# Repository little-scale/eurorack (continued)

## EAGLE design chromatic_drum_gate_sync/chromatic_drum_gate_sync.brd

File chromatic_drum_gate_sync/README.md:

This Teensy-based project has 12 gate outputs that are set using note messages over USB MIDI. 

For USB MIDI Channel 1: 

Each note in the scale (C, C#, D, D# etc) corresponds to a gate output labelled G1 - G12, and will set high from a note on message and low from a note off message. This is useful for controlling twelve drum modules using the gate input on each module. 

For USB MIDI Channel 2: 

The first six notes in the scale (C, C#, D, D# etc) corresponds to a gate output labelled G1 - G6, and will set high from a note on message and low from a note off message. A velocity above 99 will also set a gate output labelled G7 - G12 high, with a velocity below or equal to 99 will also set a gate output labelled G7 - G12 low. This is useful for controlling six drum modules using both the gate input and accent inputs on each module. 

For USB MIDI Clock: 

If a USB MIDI clock sync is sent, Gate 12 will output a short trigger upon sequencer START or CONTINUE. 
Gate 11 will output a sync signal at a rate of 12PPQN. 
Gate 10 will output a sync signal at a rate of 16th notes. 
Gate 9 will output a sync signal at a rate of 8th notes.

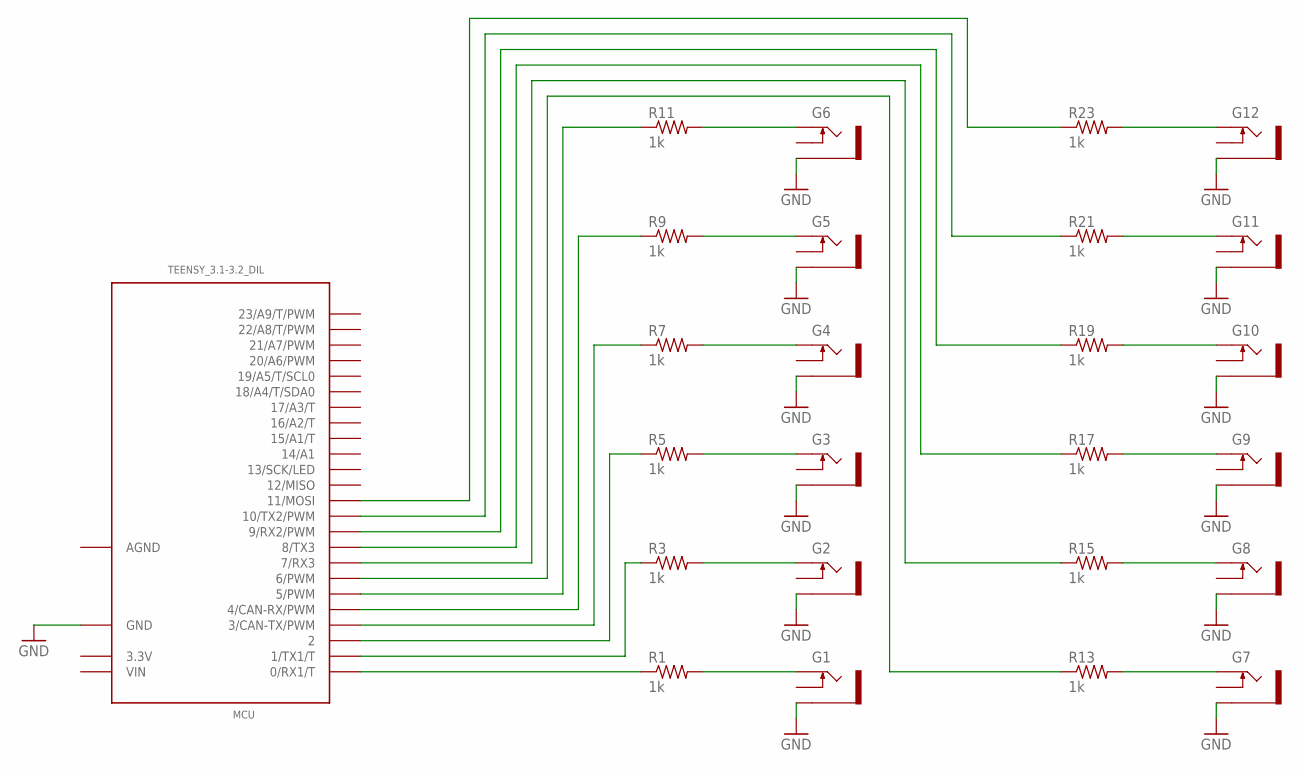
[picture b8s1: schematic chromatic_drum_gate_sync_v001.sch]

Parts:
G1, G2, G3, G4, G5, G6, G7, G8, G9, G10, G11, G12: THONKICONNNEW; WQP-PJ301M-12_JACK
MCU: TEENSY_3.1-3.2_DIL; TEENSY_3.0-3.2&LC_DIL
R1, R3, R5, R7, R9, R11, R13, R15, R17, R19, R21, R23: 1k; 0207/7

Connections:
3.3V: MCU.3.3V
AGND: MCU.AGND
GND: G1.P$3_SLEEVE (SLEEVE), G2.P$3_SLEEVE (SLEEVE), G3.P$3_SLEEVE (SLEEVE), G4.P$3_SLEEVE (SLEEVE), G5.P$3_SLEEVE (SLEEVE), G6.P$3_SLEEVE (SLEEVE), G7.P$3_SLEEVE (SLEEVE), G8.P$3_SLEEVE (SLEEVE), G9.P$3_SLEEVE (SLEEVE), G10.P$3_SLEEVE (SLEEVE), G11.P$3_SLEEVE (SLEEVE), G12.P$3_SLEEVE (SLEEVE), MCU.GND
unnamed: G1.P$1_TIP (TIP), R1.2
unnamed: G2.P$1_TIP (TIP), R3.2
unnamed: MCU.1 (1/TX1/T), R3.1
unnamed: MCU.0 (0/RX1/T), R1.1
unnamed: G3.P$1_TIP (TIP), R5.2
unnamed: MCU.2, R5.1
unnamed: G4.P$1_TIP (TIP), R7.2
unnamed: MCU.3 (3/CAN-TX/PWM), R7.1
unnamed: G5.P$1_TIP (TIP), R9.2
unnamed: MCU.4 (4/CAN-RX/PWM), R9.1
unnamed: G6.P$1_TIP (TIP), R11.2
unnamed: MCU.5 (5/PWM), R11.1
unnamed: G7.P$1_TIP (TIP), R13.2
unnamed: MCU.6 (6/PWM), R13.1
unnamed: G8.P$1_TIP (TIP), R15.2
unnamed: MCU.7 (7/RX3), R15.1
unnamed: G9.P$1_TIP (TIP), R17.2
unnamed: MCU.8 (8/TX3), R17.1
unnamed: G10.P$1_TIP (TIP), R19.2
unnamed: MCU.9 (9/RX2/PWM), R19.1
unnamed: G11.P$1_TIP (TIP), R21.2
unnamed: MCU.10 (10/TX2/PWM), R21.1
unnamed: G12.P$1_TIP (TIP), R23.2
unnamed: MCU.11 (11/MOSI), R23.1
VIN: MCU.VIN

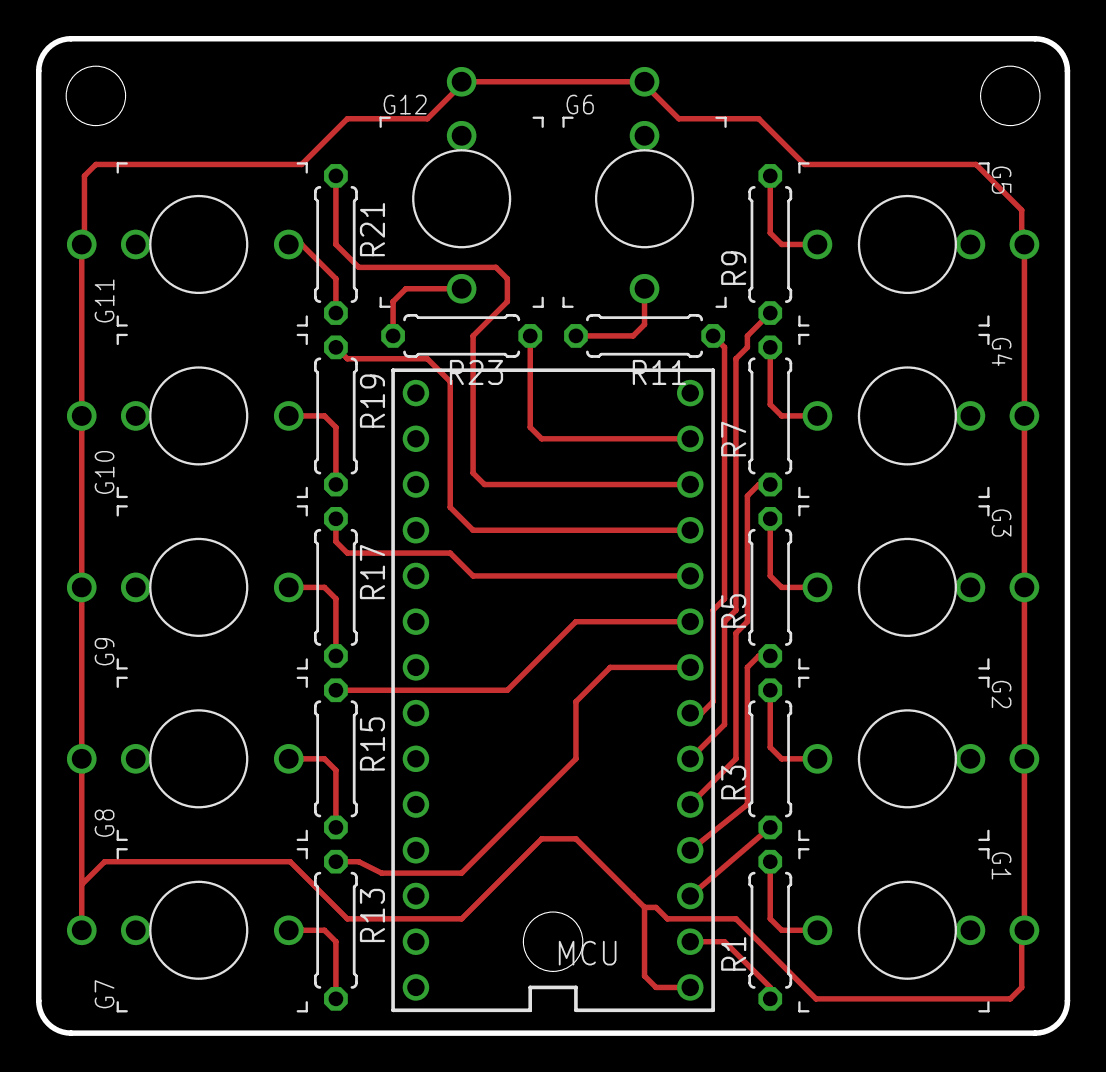
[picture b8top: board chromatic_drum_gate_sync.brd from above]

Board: 2 copper layers, 57.1 x 55.2 mm, 25 parts (0 on the bottom side), 25 nets.

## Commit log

2019-01-13 Rename Secret_Handshake_-_NanoKontrol.ino to nanokontrol.ino
2019-09-10 Rename chromatic_drum_gate_sync.sch to chromatic_drum_gate_sync_v001.sch
2020-04-15 Rename USB_MIDI_12_Gate_16_CV.ino to USB_MIDI_12_Gate_16_CV_v1.ino
